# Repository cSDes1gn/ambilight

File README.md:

# Hyperion Server Automation

Modified: 2022-01

Ansible automation for setup and teardown of hyperion servers for raspbian lite.

## Quickstart

### Setup
Install ansible
```bash
python3 -m pip install ansible
```

Run the prelink directive passing the hostname and ip address of the pi. On rasbian the default hostname is `pi`. For example:
```bash
./scripts/prelink.sh -u pi -a 192.168.2.19
```
This essentially just adds your host systems public key to the list of authorized keys on the pi which is required to run ansible. 

>By default the script will look in `~/.ssh` for an `id_rsa.pub` file but you can pass a custom ssh keypath with the -p flag:
>```bash
>./scripts/prelink.sh -u $HOSTNAME -a $IP_ADDRESS -p $SSH_KEYPATH
>```

Create an inventory file from the example to describe automation targets:
```bash
cp inventory/example.inventory.yaml inventory/inventory.yaml
```
>Be sure to update the host and target ip.

### Automation
Run hyperion server deployment automation:
```bash
ansible-playbook main.yml -e '{ teardown: False }' -K
```

And teardown:
```bash
ansible-playbook main.yml -e '{ teardown: True }' -K
```

## License
Free to use through the [MIT License](LICENSE)

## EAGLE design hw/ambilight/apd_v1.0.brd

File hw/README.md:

# Ambilight Hardware

Ambilight BOM, Power Driver and Enclosure hardware files.

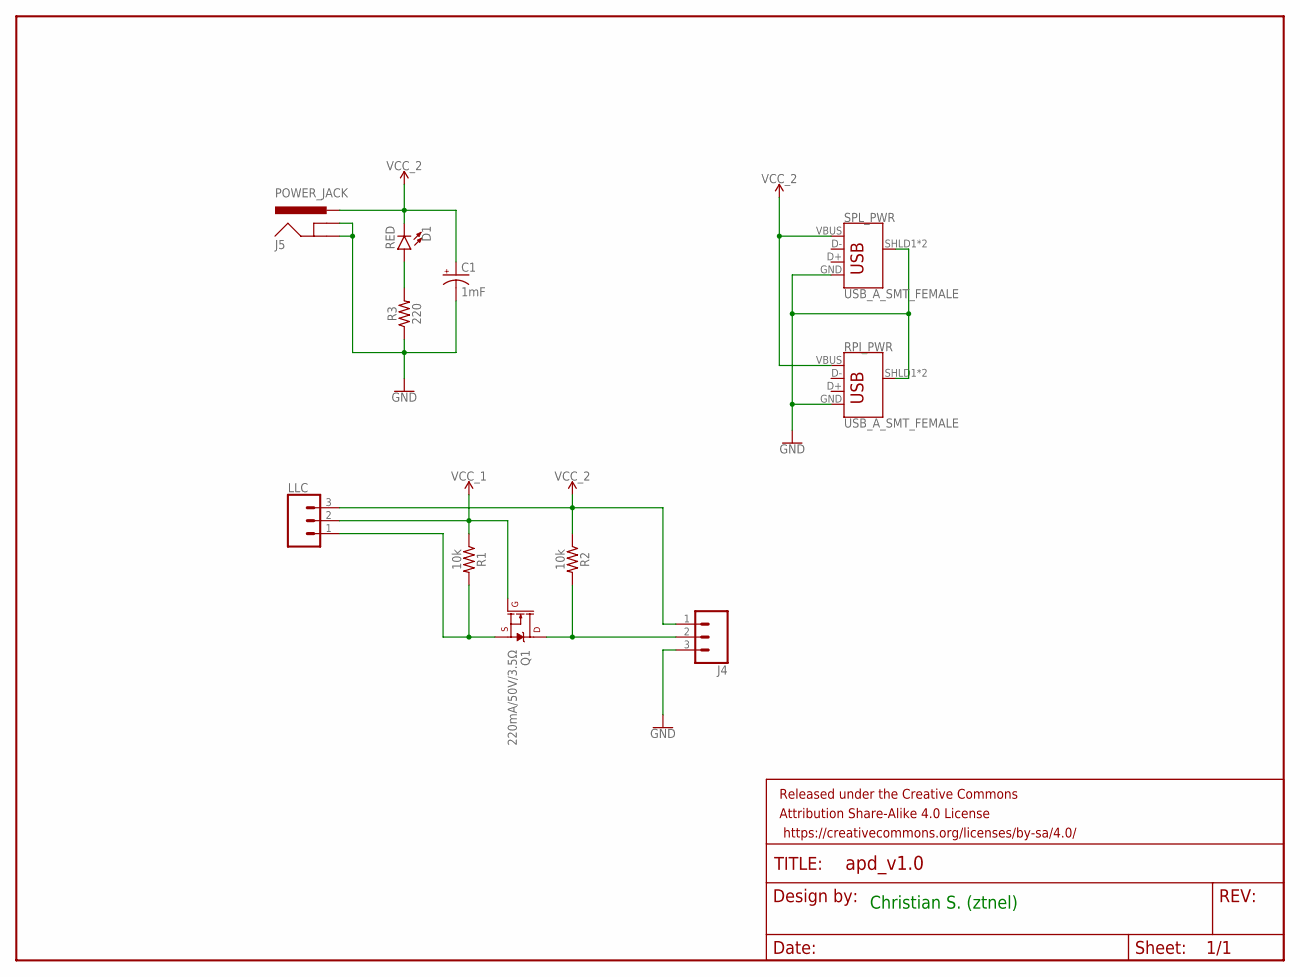
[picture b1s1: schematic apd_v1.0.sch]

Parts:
C1: 1mF; CPOL-RADIAL-5MM-10MM
D1: RED; LED-0603
FRAME1: FRAME-LETTER; CREATIVE_COMMONS
J4: CONN_03JST-PTH-VERT; JST-3-PTH-VERT
J5: POWER_JACK; POWER_JACK_PTH
LLC: CONN_03; 1X03
Q1: 220mA/50V/3.5Ω; SOT23-3
R1, R2: 10k; 0603
R3: 220; 0603
RPI_PWR: USB_A_SMT_FEMALE; USB-A-S-SILK-FEMALE
SPL_PWR: USB_A_SMT_FEMALE; USB-A-S-SILK-FEMALE

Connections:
GND: C1.-, J4.3, J5.GND, J5.GNDBREAK, R3.1, RPI_PWR.GND, RPI_PWR.SHLD1 (SHIELD), RPI_PWR.SHLD2 (SHIELD), SPL_PWR.GND, SPL_PWR.SHLD1 (SHIELD), SPL_PWR.SHLD2 (SHIELD)
unnamed: LLC.1, Q1.2 (S), R1.2
unnamed: J4.2, Q1.3 (D), R2.2
unnamed: D1.A, R3.2
VCC_1: LLC.2, Q1.1 (G), R1.1
VCC_2: C1.+, D1.C, J4.1, J5.PWR, LLC.3, R2.1, RPI_PWR.VBUS, SPL_PWR.VBUS

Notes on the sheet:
Christian S. (ztnel)

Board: 2 copper layers, 12 parts (0 on the bottom side), 6 nets, no tracks yet.

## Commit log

2021-11-05 init
2022-01-06 readme updates
2022-01-06 add prelink directive
2022-01-06 pi and general documentation
2022-01-06 cleanup readme
2022-01-06 add sample inventory
2022-01-06 stashing main yaml changes
2022-01-07 ansible and yamllint
2022-01-07 group and host cannot match
2022-01-07 remove become
2022-01-07 add -K for become
2022-01-07 rename
2022-01-07 yamllint cfg
2022-01-07 remove useless config
2022-01-07 revert become removal
2022-01-07 yamllint
2022-01-07 rename and yamllint
2022-01-07 try multiline
2022-01-07 add keypath configuration
2022-01-07 add keypath descriptor
2022-01-07 do not assume default interpreter path
2022-01-07 add hyperion role
2022-01-07 update deploy and teardown
2022-01-07 update commands
2022-01-07 add server status validation
2022-01-07 name
2022-01-07 prelink fixes
2022-01-07 readme update
2022-01-07 add inventory instructions
2022-01-07 Create LICENSE
2022-01-07 License
2022-01-07 add become
2022-01-10 some troubleshooting notes
2022-01-11 power analysis
2022-01-11 fix deploy spec (requires apt update refresh after new repo is added)
2022-01-11 BOM?
2022-01-11 apd rev 1
2022-01-12 completed v1.0 driver
2022-01-12 updated apd v1 export
2022-01-12 zipped gerber files
2022-01-12 ignore DS store
2022-04-26 assembly notes
2022-04-26 source control for brd
2022-04-27 fix interpreter path
2022-04-27 fix apt update key
2022-06-05 added 3d models to components
2022-06-05 fusion exports
2022-07-18 fusion updates
2022-08-15 stashing v1 enclosure stls
2022-08-20 move apt update and upgrade to deploy
2022-08-20 use configured username
2022-08-21 new stls
2022-08-22 spice files
2022-08-25 standoffs for pi and apd
2022-08-28 add bom
2022-08-28 update bom formatting
2022-08-28 update bom
2022-09-20 update beta enclosure

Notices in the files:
parts and their libraries:
SparkFun-Capacitors: Licensing: Creative Commons ShareAlike 4.0 International - https://creativecommons.org/licenses/by-sa/4.0
SparkFun-Aesthetics: Released under the Creative Commons Attribution Share-Alike 4.0 License
SparkFun-Aesthetics: https://creativecommons.org/licenses/by-sa/4.0
